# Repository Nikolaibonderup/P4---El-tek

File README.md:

# P4---El-tek
Projekt 4 i el teknik

#Git arkiv til p4 projekt
Dette er et git arkiv til P4---El-tek

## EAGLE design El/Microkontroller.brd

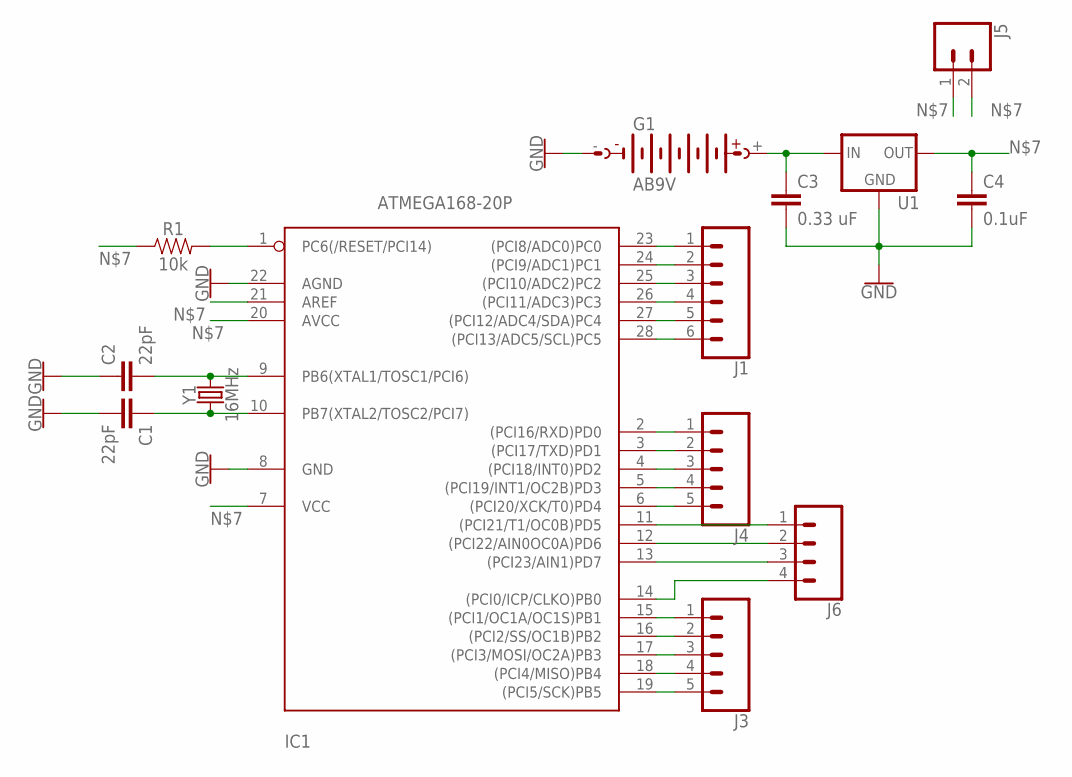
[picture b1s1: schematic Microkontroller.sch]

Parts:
C1, C2: 22pF; CAP-PTH-2.54
C3: 0.33 uF; C2.5-2
C4: 0.1uF; CAP-PTH-SMALL-KIT
G1: AB9V
IC1: ATMEGA168-20P; DIL28-3
J1: CONN_06SILK_FEMALE_PTH; 1X06
J3, J4: CONN_05; 1X05
J5: CONN_02; 1X02
J6: CONN_04; 1X04
R1: 10k; AXIAL-0.3
U1: V_REG_78XXSIDE; 78XXL
Y1: 16MHz; HC49US

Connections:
GND: C1.2, C2.1, C3.2, C4.2, G1.-, IC1.8 (GND), IC1.22 (AGND), U1.GND
unnamed: IC1.13 ((PCI23/AIN1)PD7), J6.3
unnamed: IC1.26 ((PCI11/ADC3)PC3), J1.4
unnamed: IC1.27 ((PCI12/ADC4/SDA)PC4), J1.5
unnamed: IC1.28 ((PCI13/ADC5/SCL)PC5), J1.6
unnamed: C2.2, IC1.9 (PB6(XTAL1/TOSC1/PCI6)), Y1.2
unnamed: C1.1, IC1.10 (PB7(XTAL2/TOSC2/PCI7)), Y1.1
unnamed: C4.1, IC1.7 (VCC), IC1.20 (AVCC), IC1.21 (AREF), J5.1, J5.2, R1.P$1 (1), U1.OUT
unnamed: IC1.1 (PC6(/RESET/PCI14)), R1.P$2 (2)
unnamed: C3.1, G1.+, U1.IN
unnamed: IC1.3 ((PCI17/TXD)PD1), J4.2
unnamed: IC1.2 ((PCI16/RXD)PD0), J4.1
unnamed: IC1.12 ((PCI22/AIN0OC0A)PD6), J6.2
unnamed: IC1.5 ((PCI19/INT1/OC2B)PD3), J4.4
unnamed: IC1.6 ((PCI20/XCK/T0)PD4), J4.5
unnamed: IC1.11 ((PCI21/T1/OC0B)PD5), J6.1
unnamed: IC1.4 ((PCI18/INT0)PD2), J4.3
unnamed: IC1.17 ((PCI3/MOSI/OC2A)PB3), J3.3
unnamed: IC1.18 ((PCI4/MISO)PB4), J3.4
unnamed: IC1.19 ((PCI5/SCK)PB5), J3.5
unnamed: IC1.14 ((PCI0/ICP/CLKO)PB0), J6.4
unnamed: IC1.15 ((PCI1/OC1A/OC1S)PB1), J3.1
unnamed: IC1.16 ((PCI2/SS/OC1B)PB2), J3.2
unnamed: IC1.25 ((PCI10/ADC2)PC2), J1.3
unnamed: IC1.24 ((PCI9/ADC1)PC1), J1.2
unnamed: IC1.23 ((PCI8/ADC0)PC0), J1.1

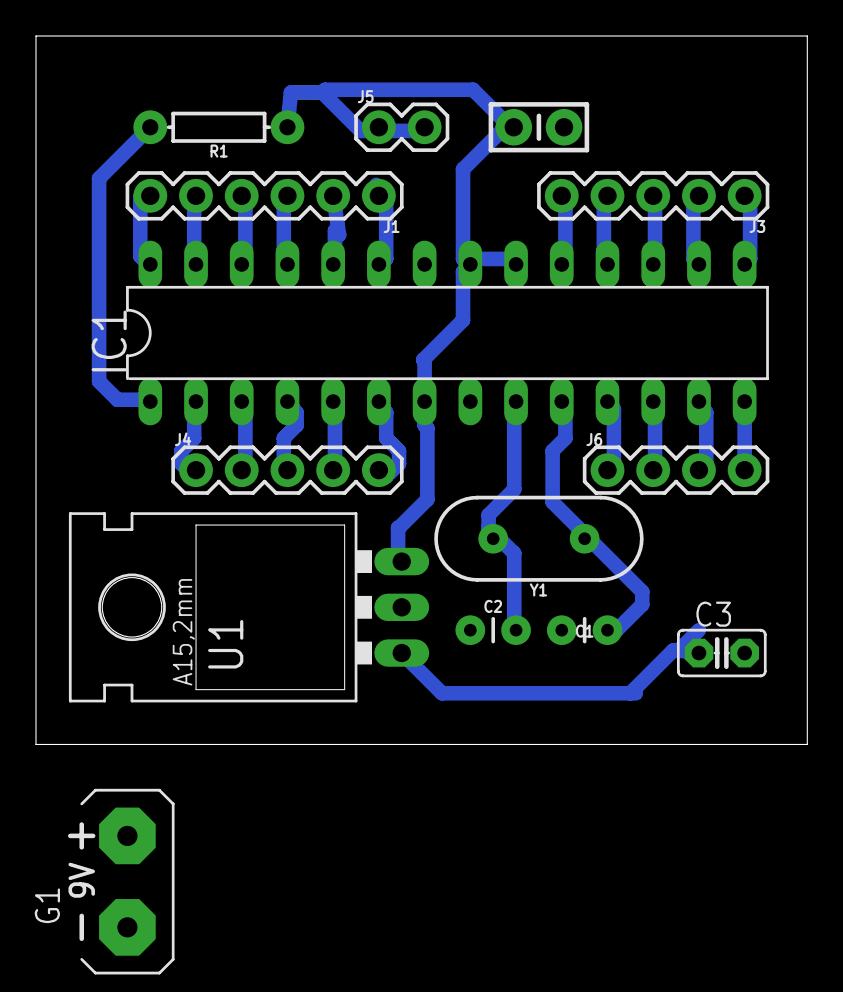
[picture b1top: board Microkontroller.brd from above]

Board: 2 copper layers, 42.8 x 39.4 mm, 14 parts (0 on the bottom side), 26 nets.

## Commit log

2018-11-15 Initial commit. Changed README.MD
2018-11-15 Tilføjet Main.tex
2018-11-20 Projektbeskrivelse
2018-11-20 Alt layout til projektbeskrivelse lavet
2018-11-20 Forside
2018-11-22 fikset forside
2018-11-22 Ændringer jeg ikke kan huske
2018-11-23 Fix af forsidens vejledere
2018-11-23 tidsplan
2018-11-23 Alt tekst indsat, samt indledning oprettet
2018-11-25 Opsat hele dokumentet
2018-11-25 Sidste retninger
2018-12-05 kode
2018-12-17 Tilføjet rapport
2018-12-18 Fysik rapport shit
2018-12-19 Mere teori
2018-12-19 Semi-finish
2019-01-23 El-diagram, PCB + billeder
2019-01-23 Forbedret el-diagram + billede
2019-01-24 Har tilfoejet kode til controller og turret
2019-01-24 Knap håndterings kode
2019-01-28 Fysikdata
2019-01-28 Fysikting igen
2019-01-30 Random stuff
2019-02-01 kode - rettet
2019-02-05 Billeder
2019-02-05 Kode done
2019-02-05 Billeder af print
2019-02-06 Færdiggjort rapport
2019-02-27 måleresultater
2019-03-25 Fysik

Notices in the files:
parts and their libraries:
SparkFun-Capacitors: Licensing: Creative Commons ShareAlike 4.0 International - https://creativecommons.org/licenses/by-sa/4.0
